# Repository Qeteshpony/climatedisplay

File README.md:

# Climate Display

[Hardware Documentation](https://qeteshpony.github.io/climatedisplay)

Complete overhaul of one of my earlier electronics projects! A display that is running here for years, back then made completely with THT components on a crude pcb. It shows the temperature and dew point for the room and outdoor sensors. 

I learned a lot about pcb design since then and was not happy with the look of the old device so I remade the whole device in a way that keeps the general look but a lot more fancy, moving everything but the display elements to the back of the board, adding a 3d-printed frame, replacing the barrel connector with USB-C and many more little things. 

The old version also had the digits of the displays backwards which didnt matter when I wrote the arduino script to run it. But now I want to use ESP-Home so they have to be wired correctly ;)

Every other dual-7-segment module is upside down so the decimal dot on the last digit in each row can be used as a ° symbol.

The original project was documented on my blog: https://electronics.qetesh.de/climate-display/

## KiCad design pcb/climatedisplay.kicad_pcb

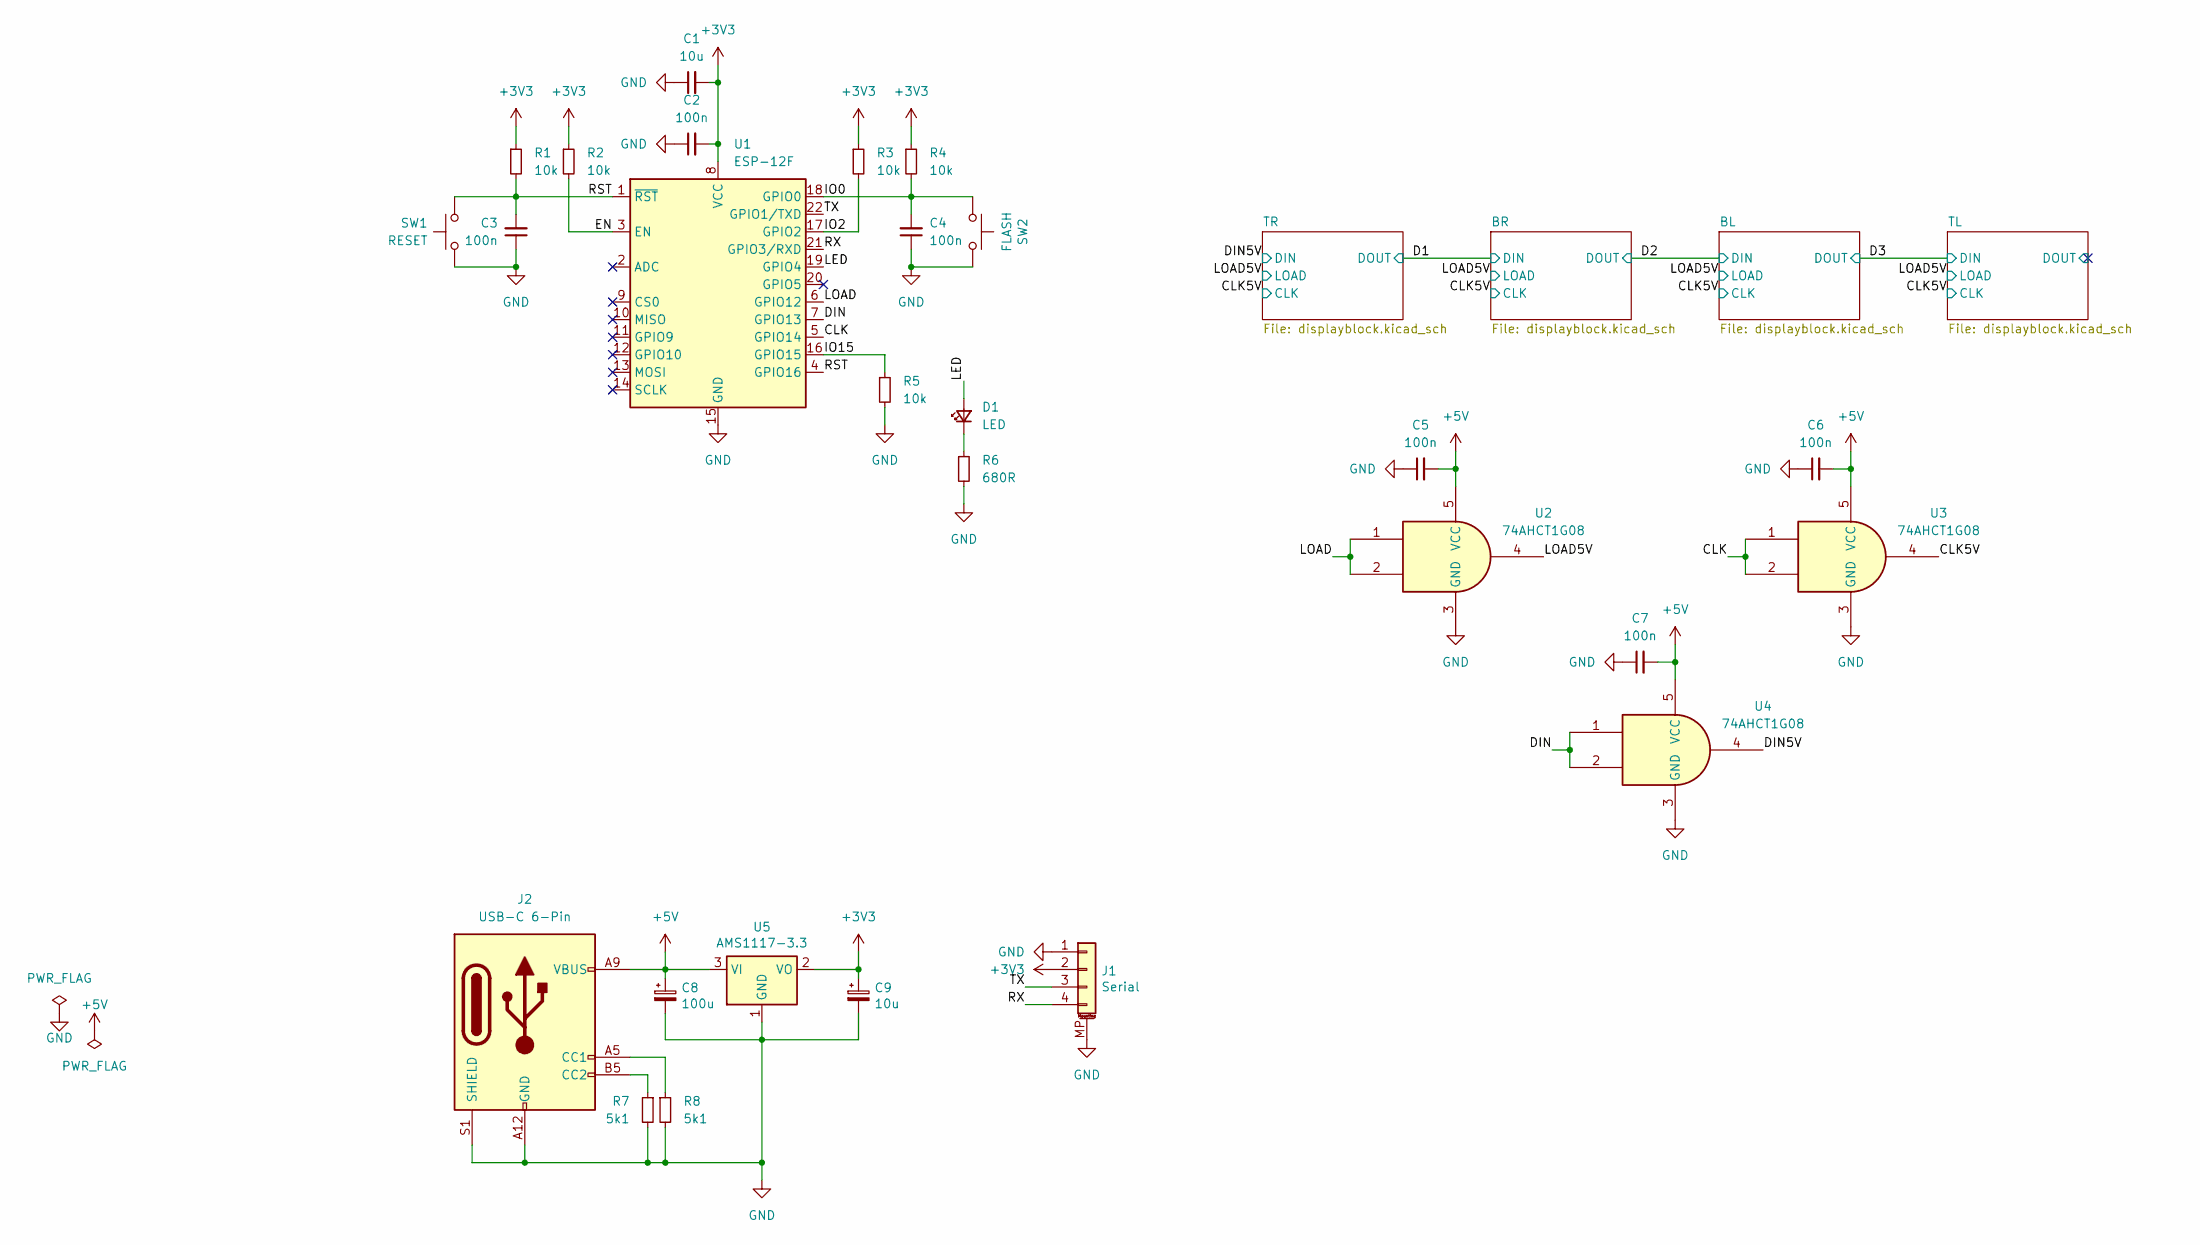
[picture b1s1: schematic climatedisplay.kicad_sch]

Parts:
C1: 10u; C_0402_1005Metric; LCSC C15525
C2, C3, C4, C5, C6, C7: 100n; C_0402_1005Metric; LCSC C1525
C8: 100u; CP_EIA-3528-21_Kemet-B; LCSC C16133
C9: 10u; CP_EIA-3216-18_Kemet-A; LCSC C7171
D1: LED; LED_0603_1608Metric; LCSC C2286
J1: Serial; JST_PH_S4B-PH-SM4-TB_1x04-1MP_P2.00mm_Horizontal
J2: USB-C 6-Pin; GCT_USB4130-GF-A_REVA
R1, R2, R3, R4, R5: 10k; R_0402_1005Metric; LCSC C25744
R6: 680R; R_0402_1005Metric; LCSC C25130
R7, R8: 5k1; R_0402_1005Metric; LCSC C25905
SW1: RESET; SW_Push_1P1T_XKB_TS-1187A; LCSC C318884
SW2: FLASH; SW_Push_1P1T_XKB_TS-1187A; LCSC C318884
U1: ESP-12F; ESP-12E
U2, U3, U4: 74AHCT1G08; SOT-353_SC-70-5; LCSC C455047
U5: AMS1117-3.3; SOT-223-3_TabPin2; LCSC C6186

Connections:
+3V3: C1.2, C2.2, C9.1, J1.2, R1.1, R2.1, R3.1, R4.1, U1.8 (VCC), U5.2 (VO)
+5V: C5.2, C6.2, C7.2, C8.1, J2.A9 (VBUS), J2.B9 (VBUS), U2.5 (VCC), U3.5 (VCC), U4.5 (VCC), U5.3 (VI); also elsewhere on the board
/CLK: U1.5 (GPIO14), U3.1, U3.2
/CLK5V: U3.4; also elsewhere on the board
/DIN: U1.7 (GPIO13), U4.1, U4.2
/DIN5V: U4.4; also elsewhere on the board
/EN: R2.2, U1.3 (EN)
/IO0: C4.2, R4.2, SW2.1, U1.18 (GPIO0)
/IO2: R3.2, U1.17 (GPIO2)
/IO15: R5.1, U1.16 (GPIO15)
/LED: D1.2 (A), U1.19 (GPIO4)
/LOAD: U1.6 (GPIO12), U2.1, U2.2
/LOAD5V: U2.4; also elsewhere on the board
/RST: C3.2, R1.2, SW1.2, U1.1 (~RST), U1.4 (GPIO16)
/RX: J1.4, U1.21 (GPIO3/RXD)
/TX: J1.3, U1.22 (GPIO1/TXD)
GND: C1.1, C2.1, C3.1, C4.1, C5.1, C6.1, C7.1, C8.2, C9.2, J1.1, J1.MP (MountPin), J2.A12 (GND), J2.B12 (GND), J2.S1 (SHIELD), R5.2, R6.2, R7.2, R8.2, SW1.1, SW2.2, U1.15 (GND), U2.3 (GND), U3.3 (GND), U4.3 (GND), U5.1 (GND); also elsewhere on the board
unnamed: D1.1 (K), R6.1
unnamed: J2.A5 (CC1), R8.1
unnamed: J2.B5 (CC2), R7.1

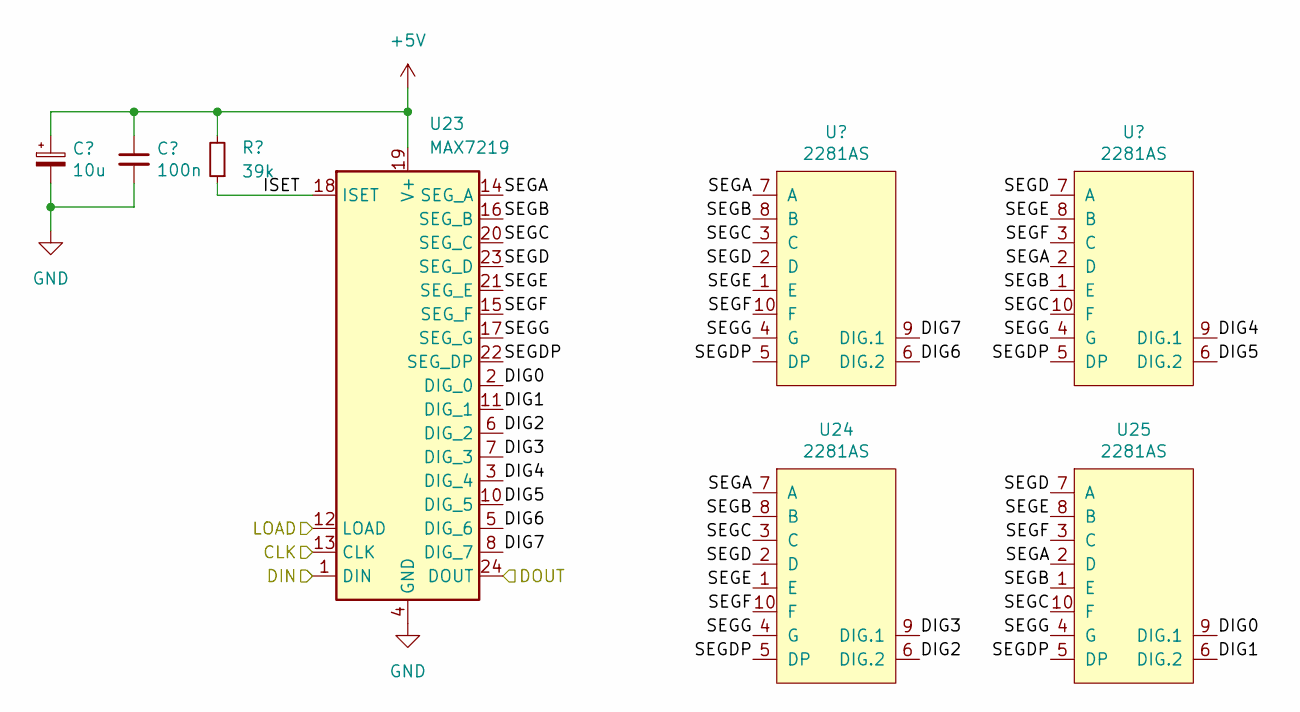
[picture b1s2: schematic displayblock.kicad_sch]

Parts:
C16: 10u; CP_EIA-3216-18_Kemet-A; LCSC C7171
C17: 100n; C_0402_1005Metric; LCSC C1525
R12: 39k; R_0402_1005Metric; LCSC C25783
U21, U22, U24, U25: 2281AS; 2281AS_BS
U23: MAX7219; SOP-24_7.5x15.4mm_P1.27mm; LCSC C9964

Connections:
+5V: C16.1, C17.1, R12.2, U23.19 (V+); also elsewhere on the board
/CLK5V: U23.13 (CLK); also elsewhere on the board
/D3: U23.1 (DIN); also elsewhere on the board
/LOAD5V: U23.12 (LOAD); also elsewhere on the board
/TL/DIG0: U23.2 (DIG_0), U25.9 (DIG.1)
/TL/DIG1: U23.11 (DIG_1), U25.6 (DIG.2)
/TL/DIG2: U23.6 (DIG_2), U24.6 (DIG.2)
/TL/DIG3: U23.7 (DIG_3), U24.9 (DIG.1)
/TL/DIG4: U22.9 (DIG.1), U23.3 (DIG_4)
/TL/DIG5: U22.6 (DIG.2), U23.10 (DIG_5)
/TL/DIG6: U21.6 (DIG.2), U23.5 (DIG_6)
/TL/DIG7: U21.9 (DIG.1), U23.8 (DIG_7)
/TL/DOUT: U23.24 (DOUT)
/TL/ISET: R12.1, U23.18 (ISET)
/TL/SEGA: U21.7 (A), U22.2 (D), U23.14 (SEG_A), U24.7 (A), U25.2 (D)
/TL/SEGB: U21.8 (B), U22.1 (E), U23.16 (SEG_B), U24.8 (B), U25.1 (E)
/TL/SEGC: U21.3 (C), U22.10 (F), U23.20 (SEG_C), U24.3 (C), U25.10 (F)
/TL/SEGD: U21.2 (D), U22.7 (A), U23.23 (SEG_D), U24.2 (D), U25.7 (A)
/TL/SEGDP: U21.5 (DP), U22.5 (DP), U23.22 (SEG_DP), U24.5 (DP), U25.5 (DP)
/TL/SEGE: U21.1 (E), U22.8 (B), U23.21 (SEG_E), U24.1 (E), U25.8 (B)
/TL/SEGF: U21.10 (F), U22.3 (C), U23.15 (SEG_F), U24.10 (F), U25.3 (C)
/TL/SEGG: U21.4 (G), U22.4 (G), U23.17 (SEG_G), U24.4 (G), U25.4 (G)
GND: C16.2, C17.2, U23.4 (GND), U23.9 (GND); also elsewhere on the board

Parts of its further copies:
C10, C12, C14: 10u; CP_EIA-3216-18_Kemet-A; LCSC C7171
C11, C13, C15: 100n; C_0402_1005Metric; LCSC C1525
R9, R10, R11: 39k; R_0402_1005Metric; LCSC C25783
U6, U7, U9, U10, U11, U12, U14, U15, U16, U17, U19, U20: 2281AS; 2281AS_BS
U8, U13, U18: MAX7219; SOP-24_7.5x15.4mm_P1.27mm; LCSC C9964

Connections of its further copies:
+5V: C10.1, C11.1, C12.1, C13.1, C14.1, C15.1, R9.2, R10.2, R11.2, U8.19 (V+), U13.19 (V+), U18.19 (V+); also elsewhere on the board
/BL/DIG0: U18.2 (DIG_0), U20.9 (DIG.1)
/BL/DIG1: U18.11 (DIG_1), U20.6 (DIG.2)
/BL/DIG2: U18.6 (DIG_2), U19.6 (DIG.2)
/BL/DIG3: U18.7 (DIG_3), U19.9 (DIG.1)
/BL/DIG4: U17.9 (DIG.1), U18.3 (DIG_4)
/BL/DIG5: U17.6 (DIG.2), U18.10 (DIG_5)
/BL/DIG6: U16.6 (DIG.2), U18.5 (DIG_6)
/BL/DIG7: U16.9 (DIG.1), U18.8 (DIG_7)
/BL/ISET: R11.1, U18.18 (ISET)
/BL/SEGA: U16.7 (A), U17.2 (D), U18.14 (SEG_A), U19.7 (A), U20.2 (D)
/BL/SEGB: U16.8 (B), U17.1 (E), U18.16 (SEG_B), U19.8 (B), U20.1 (E)
/BL/SEGC: U16.3 (C), U17.10 (F), U18.20 (SEG_C), U19.3 (C), U20.10 (F)
/BL/SEGD: U16.2 (D), U17.7 (A), U18.23 (SEG_D), U19.2 (D), U20.7 (A)
/BL/SEGDP: U16.5 (DP), U17.5 (DP), U18.22 (SEG_DP), U19.5 (DP), U20.5 (DP)
/BL/SEGE: U16.1 (E), U17.8 (B), U18.21 (SEG_E), U19.1 (E), U20.8 (B)
/BL/SEGF: U16.10 (F), U17.3 (C), U18.15 (SEG_F), U19.10 (F), U20.3 (C)
/BL/SEGG: U16.4 (G), U17.4 (G), U18.17 (SEG_G), U19.4 (G), U20.4 (G)
/BR/DIG0: U13.2 (DIG_0), U15.9 (DIG.1)
/BR/DIG1: U13.11 (DIG_1), U15.6 (DIG.2)
/BR/DIG2: U13.6 (DIG_2), U14.6 (DIG.2)
/BR/DIG3: U13.7 (DIG_3), U14.9 (DIG.1)
/BR/DIG4: U12.9 (DIG.1), U13.3 (DIG_4)
/BR/DIG5: U12.6 (DIG.2), U13.10 (DIG_5)
/BR/DIG6: U11.6 (DIG.2), U13.5 (DIG_6)
/BR/DIG7: U11.9 (DIG.1), U13.8 (DIG_7)
/BR/ISET: R10.1, U13.18 (ISET)
/BR/SEGA: U11.7 (A), U12.2 (D), U13.14 (SEG_A), U14.7 (A), U15.2 (D)
/BR/SEGB: U11.8 (B), U12.1 (E), U13.16 (SEG_B), U14.8 (B), U15.1 (E)
/BR/SEGC: U11.3 (C), U12.10 (F), U13.20 (SEG_C), U14.3 (C), U15.10 (F)
/BR/SEGD: U11.2 (D), U12.7 (A), U13.23 (SEG_D), U14.2 (D), U15.7 (A)
/BR/SEGDP: U11.5 (DP), U12.5 (DP), U13.22 (SEG_DP), U14.5 (DP), U15.5 (DP)
/BR/SEGE: U11.1 (E), U12.8 (B), U13.21 (SEG_E), U14.1 (E), U15.8 (B)
/BR/SEGF: U11.10 (F), U12.3 (C), U13.15 (SEG_F), U14.10 (F), U15.3 (C)
/BR/SEGG: U11.4 (G), U12.4 (G), U13.17 (SEG_G), U14.4 (G), U15.4 (G)
/CLK5V: U8.13 (CLK), U13.13 (CLK), U18.13 (CLK); also elsewhere on the board
/D1: U8.24 (DOUT), U13.1 (DIN)
/D2: U13.24 (DOUT), U18.1 (DIN)
/D3: U18.24 (DOUT); also elsewhere on the board
/DIN5V: U8.1 (DIN); also elsewhere on the board
/LOAD5V: U8.12 (LOAD), U13.12 (LOAD), U18.12 (LOAD); also elsewhere on the board
/TR/DIG0: U8.2 (DIG_0), U10.9 (DIG.1)
/TR/DIG1: U8.11 (DIG_1), U10.6 (DIG.2)
/TR/DIG2: U8.6 (DIG_2), U9.6 (DIG.2)
/TR/DIG3: U8.7 (DIG_3), U9.9 (DIG.1)
/TR/DIG4: U7.9 (DIG.1), U8.3 (DIG_4)
/TR/DIG5: U7.6 (DIG.2), U8.10 (DIG_5)
/TR/DIG6: U6.6 (DIG.2), U8.5 (DIG_6)
/TR/DIG7: U6.9 (DIG.1), U8.8 (DIG_7)
/TR/ISET: R9.1, U8.18 (ISET)
/TR/SEGA: U6.7 (A), U7.2 (D), U8.14 (SEG_A), U9.7 (A), U10.2 (D)
/TR/SEGB: U6.8 (B), U7.1 (E), U8.16 (SEG_B), U9.8 (B), U10.1 (E)
/TR/SEGC: U6.3 (C), U7.10 (F), U8.20 (SEG_C), U9.3 (C), U10.10 (F)
/TR/SEGD: U6.2 (D), U7.7 (A), U8.23 (SEG_D), U9.2 (D), U10.7 (A)
/TR/SEGDP: U6.5 (DP), U7.5 (DP), U8.22 (SEG_DP), U9.5 (DP), U10.5 (DP)
/TR/SEGE: U6.1 (E), U7.8 (B), U8.21 (SEG_E), U9.1 (E), U10.8 (B)
/TR/SEGF: U6.10 (F), U7.3 (C), U8.15 (SEG_F), U9.10 (F), U10.3 (C)
/TR/SEGG: U6.4 (G), U7.4 (G), U8.17 (SEG_G), U9.4 (G), U10.4 (G)
GND: C10.2, C11.2, C12.2, C13.2, C14.2, C15.2, U8.4 (GND), U8.9 (GND), U13.4 (GND), U13.9 (GND), U18.4 (GND), U18.9 (GND); also elsewhere on the board

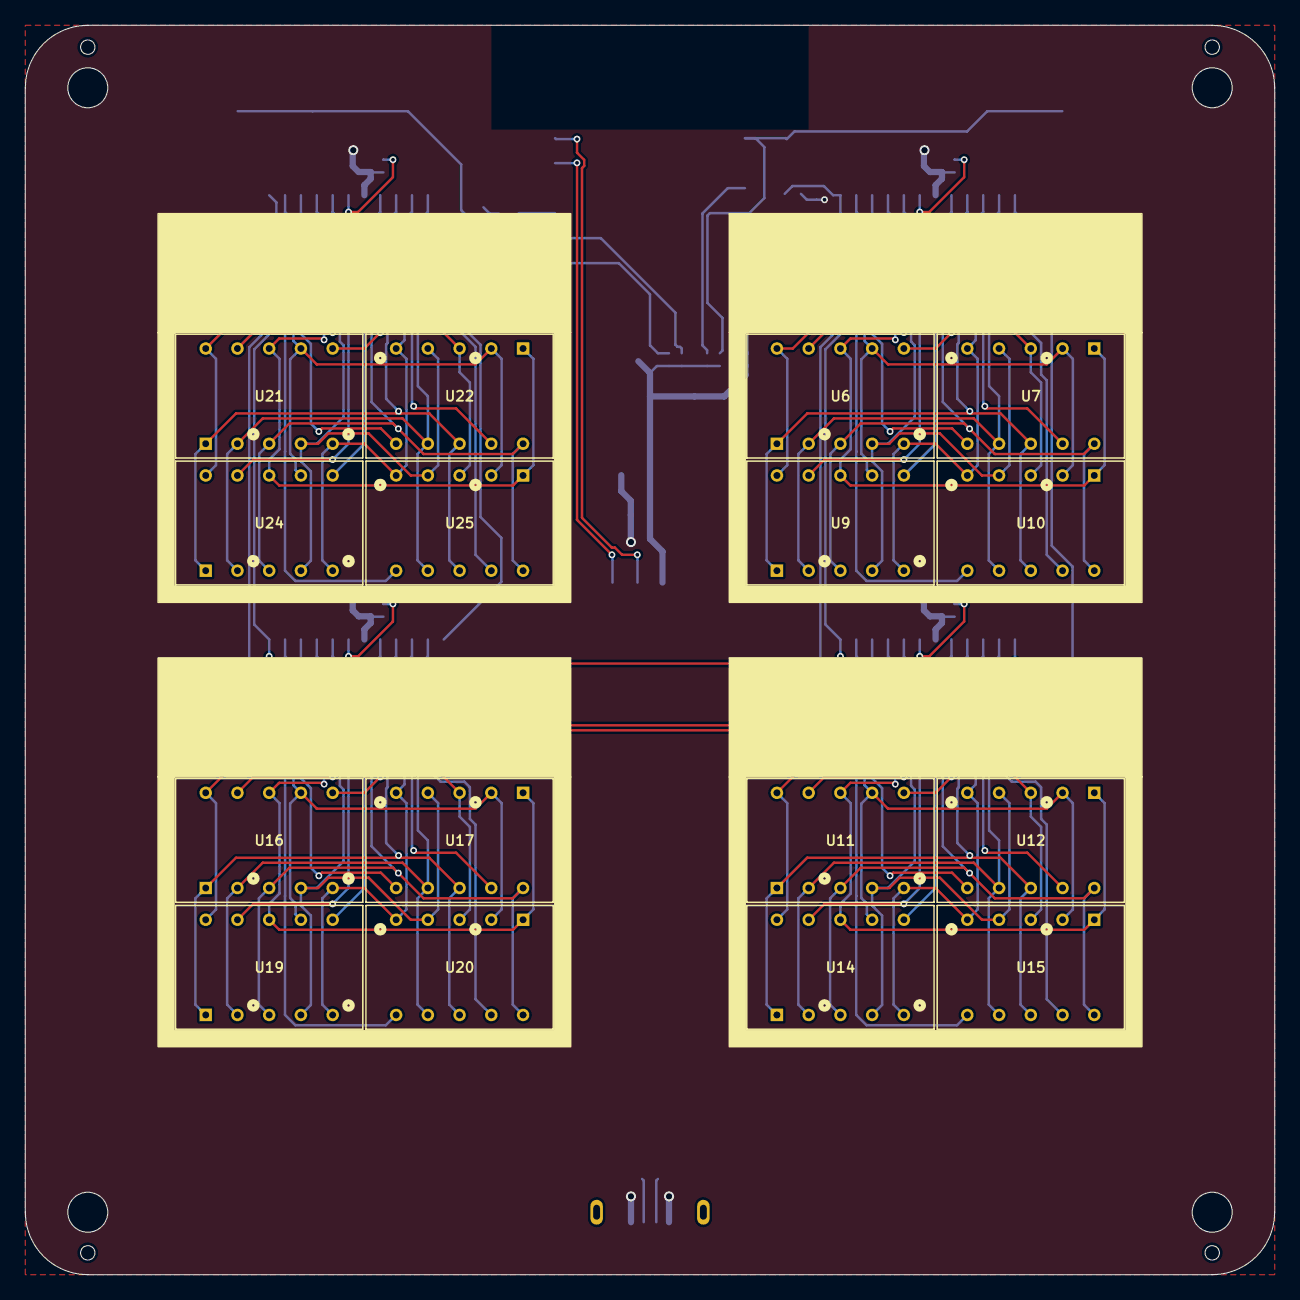
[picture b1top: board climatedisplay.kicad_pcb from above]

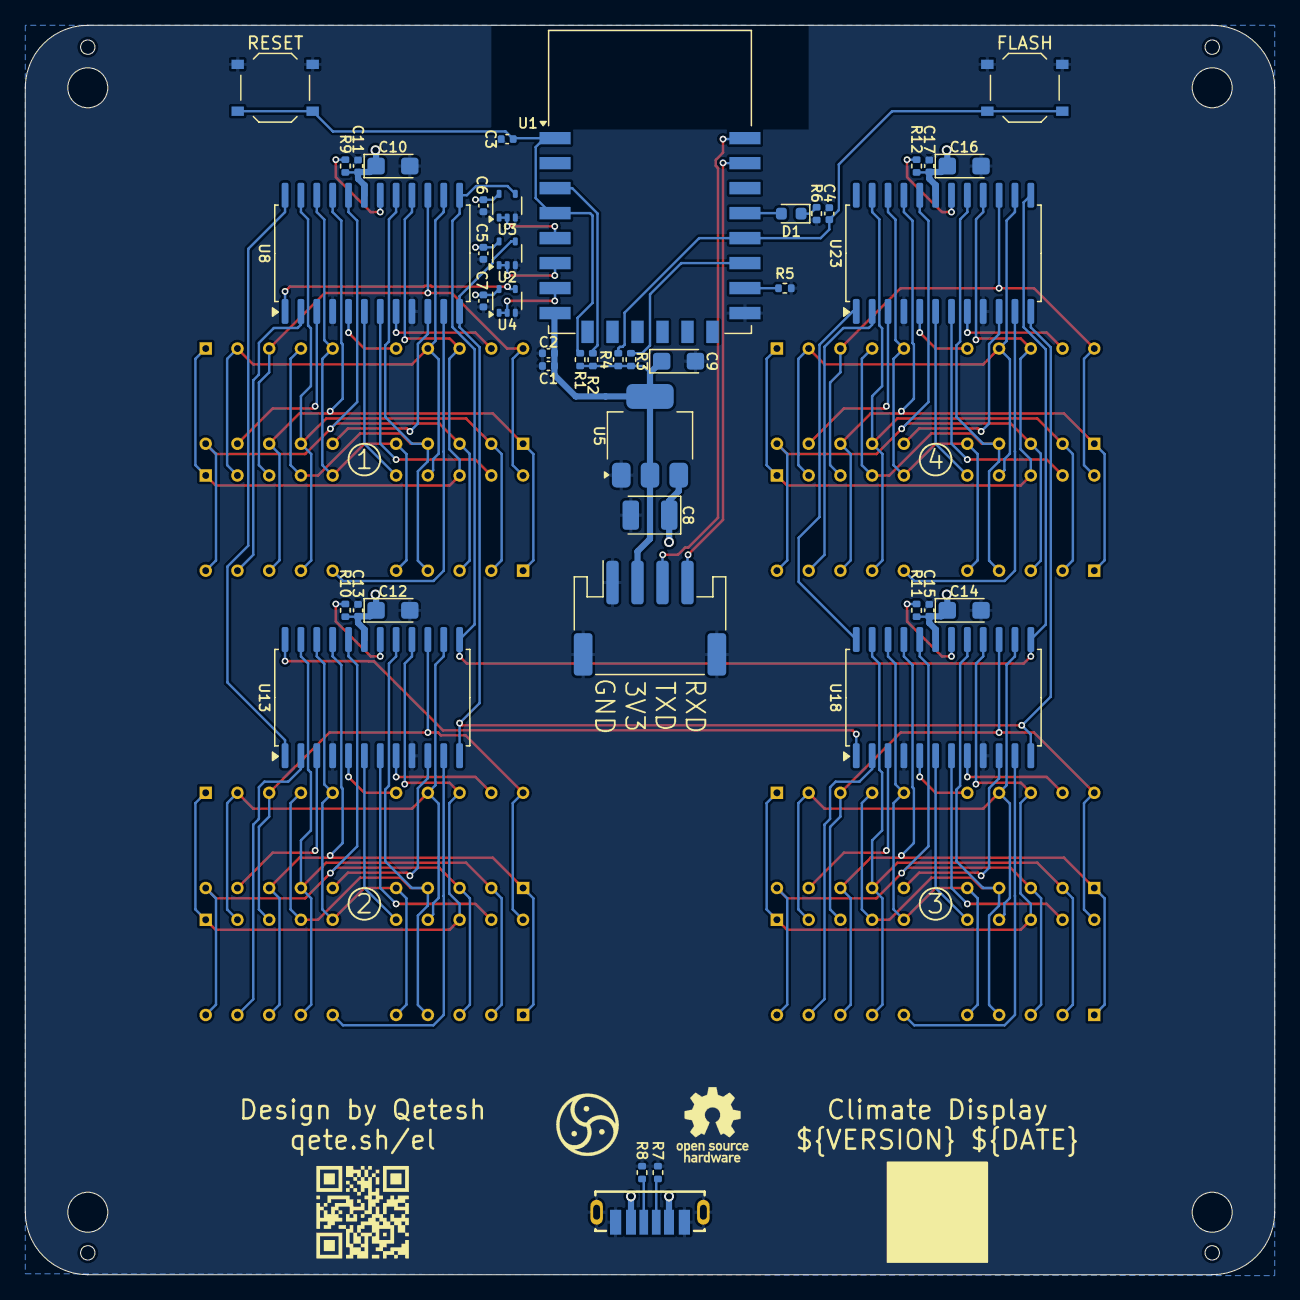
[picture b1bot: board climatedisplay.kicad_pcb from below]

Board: 2 copper layers, 100.0 x 100.0 mm, 59 parts (43 on the bottom side), 91 nets.

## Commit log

2024-09-04 feat: initial commit
2024-09-04 chore(main): release 1.0.0
2024-09-04 fix: footprints U2-U4
2024-09-04 chore(main): release 1.0.1
